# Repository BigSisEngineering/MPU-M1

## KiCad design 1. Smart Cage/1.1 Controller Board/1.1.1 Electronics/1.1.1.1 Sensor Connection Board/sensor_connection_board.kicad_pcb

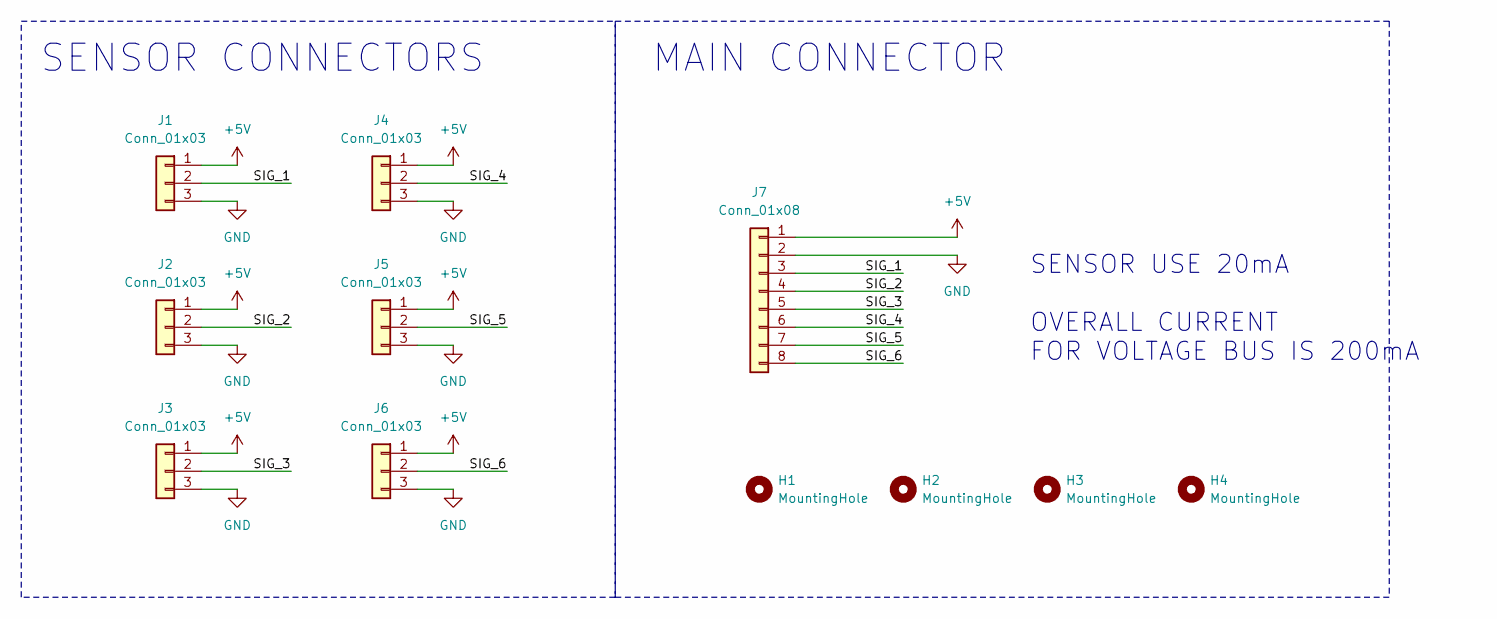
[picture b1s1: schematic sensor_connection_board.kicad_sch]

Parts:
H1, H2, H3, H4: MountingHole; MountingHole_3.2mm_M3_ISO7380
J1, J2, J3, J4, J5, J6: Conn_01x03; JST_PH_B3B-PH-K_1x03_P2.00mm_Vertical; LCSC C131339
J7: Conn_01x08; JST_PH_B8B-PH-K_1x08_P2.00mm_Vertical; LCSC C157974

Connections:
+5V: J1.1, J2.1, J3.1, J4.1, J5.1, J6.1, J7.1
/SIG_1: J1.2, J7.3
/SIG_2: J2.2, J7.4
/SIG_3: J3.2, J7.5
/SIG_4: J4.2, J7.6
/SIG_5: J5.2, J7.7
/SIG_6: J6.2, J7.8
GND: J1.3, J2.3, J3.3, J4.3, J5.3, J6.3, J7.2

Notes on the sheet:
MAIN CONNECTOR
SENSOR USE 20mA OVERALL CURRENT FOR VOLTAGE BUS IS 200mA
SENSOR CONNECTORS

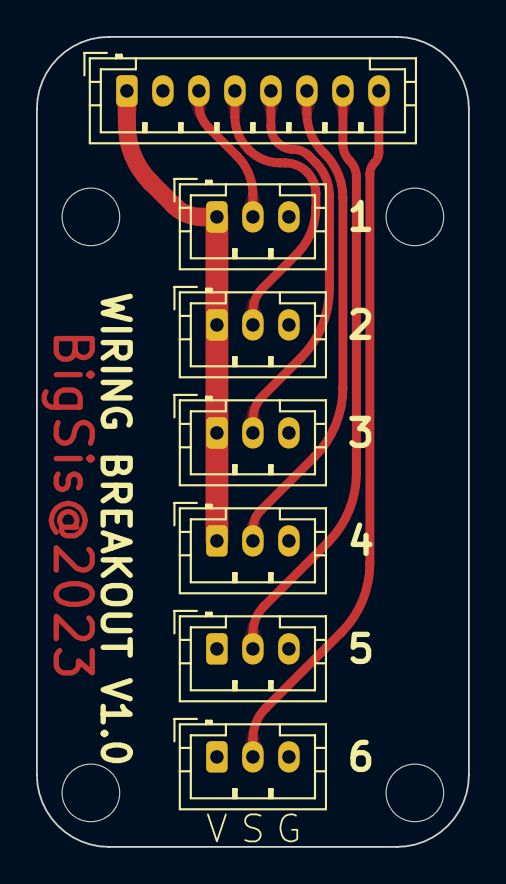
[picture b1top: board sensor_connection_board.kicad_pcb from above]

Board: 2 copper layers, 24.0 x 45.0 mm, 11 parts (0 on the bottom side), 8 nets.

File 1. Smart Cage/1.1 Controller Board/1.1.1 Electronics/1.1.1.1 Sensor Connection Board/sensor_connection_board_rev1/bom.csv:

Designator,Footprint,Quantity,Value,LCSC Part #
"H1, H2, H3, H4",MountingHole_3.2mm_M3_ISO7380,4,MountingHole,
"J1, J2, J3, J4, J5, J6",JST_PH_B3B-PH-K_1x03_P2.00mm_Vertical,6,Conn_01x03,C131339
J7,JST_PH_B8B-PH-K_1x08_P2.00mm_Vertical,1,Conn_01x08,C157974

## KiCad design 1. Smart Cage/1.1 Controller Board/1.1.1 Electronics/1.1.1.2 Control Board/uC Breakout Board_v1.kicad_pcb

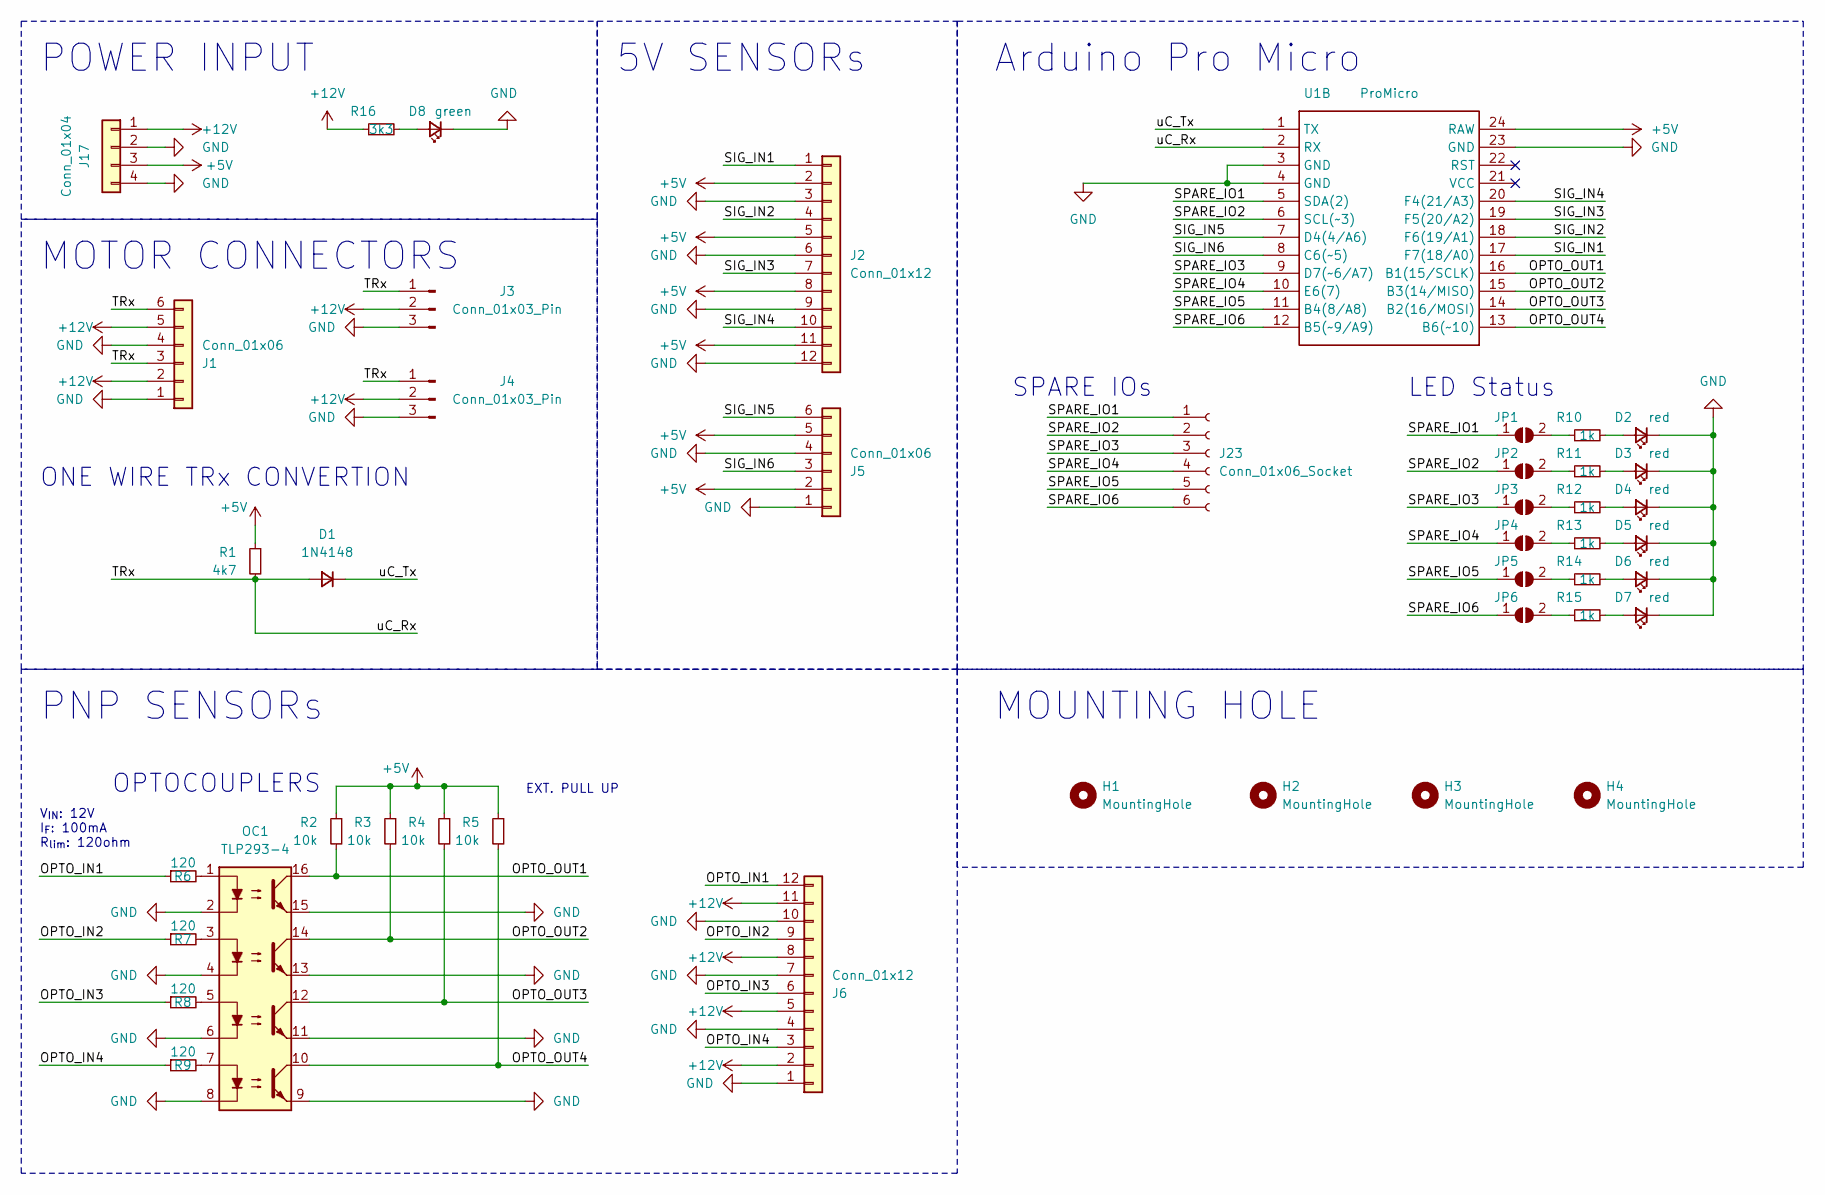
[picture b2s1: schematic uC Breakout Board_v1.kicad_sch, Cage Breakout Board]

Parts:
D1: 1N4148; D_SOD-123; LCSC C81598
D2, D3, D4, D5, D6, D7: red; LED_0805_2012Metric_Pad1.15x1.40mm_HandSolder; LCSC C434431
D8: green; LED_0805_2012Metric_Pad1.15x1.40mm_HandSolder; LCSC C434435
H1, H2, H3, H4: MountingHole; MountingHole_3.2mm_M3_ISO7380
J1, J5: Conn_01x06; DB142R-5.08-6P; LCSC C2898713
J2, J6: Conn_01x12; DB142R-5.08-12P; LCSC C2898718
J3, J4: Conn_01x03_Pin; PinSocket_1x03_P2.54mm_Vertical
J17: Conn_01x04; DB142R-5.08-4P; LCSC C2898711
J23: Conn_01x06_Socket; PinHeader_1x06_P2.54mm_Vertical
JP1, JP2, JP3, JP4, JP5, JP6: SolderJumper_2_Open; SolderJumper-2_P1.3mm_Open_TrianglePad1.0x1.5mm
OC1: TLP293-4; SOIC-16W_5.3x10.2mm_P1.27mm; LCSC C3002262
R1: 4k7; R_0805_2012Metric_Pad1.20x1.40mm_HandSolder; LCSC C229219
R2, R3, R4, R5: 10k; R_0805_2012Metric_Pad1.20x1.40mm_HandSolder; LCSC C84376
R6, R7, R8, R9: 120; R_0805_2012Metric_Pad1.20x1.40mm_HandSolder; LCSC C114244
R10, R11, R12, R13, R14, R15: 1k; R_0805_2012Metric_Pad1.20x1.40mm_HandSolder; LCSC C95781
R16: 3k3; R_0805_2012Metric_Pad1.20x1.40mm_HandSolder; LCSC C114531
U1: ProMicro; ProMicro-2x12-Header-B; LCSC C3975157
U2: ProMicro; ProMirco-2x12-Header-A; LCSC C3975157

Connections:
+5V: J2.2, J2.5, J2.8, J2.11, J5.2, J5.5, J17.3, R1.1, R2.1, R3.1, R4.1, R5.1, U1.24 (RAW)
+12V: J1.2, J1.5, J3.2, J4.2, J6.2, J6.5, J6.8, J6.11, J17.1, R16.1
/OPTO_IN1: J6.12, R6.1
/OPTO_IN2: J6.9, R7.1
/OPTO_IN3: J6.6, R8.1
/OPTO_IN4: J6.3, R9.1
/OPTO_OUT1: OC1.16, R2.2, U1.16 (B1(15/SCLK))
/OPTO_OUT2: OC1.14, R3.2, U1.15 (B3(14/MISO))
/OPTO_OUT3: OC1.12, R4.2, U1.14 (B2(16/MOSI))
/OPTO_OUT4: OC1.10, R5.2, U1.13 (B6(~10))
/SIG_IN1: J2.1, U1.17 (F7(18/A0))
/SIG_IN2: J2.4, U1.18 (F6(19/A1))
/SIG_IN3: J2.7, U1.19 (F5(20/A2))
/SIG_IN4: J2.10, U1.20 (F4(21/A3))
/SIG_IN5: J5.6, U2.7 (D4(4/A6))
/SIG_IN6: J5.3, U2.8 (C6(~5))
/SPARE_IO1: J23.1, JP1.1 (A), U2.5 (SDA(2))
/SPARE_IO2: J23.2, JP2.1 (A), U2.6 (SCL(~3))
/SPARE_IO3: J23.3, JP3.1 (A), U2.9 (D7(~6/A7))
/SPARE_IO4: J23.4, JP4.1 (A), U2.10 (E6(7))
/SPARE_IO5: J23.5, JP5.1 (A), U2.11 (B4(8/A8))
/SPARE_IO6: J23.6, JP6.1 (A), U2.12 (B5(~9/A9))
/TRx: D1.2 (A), J1.3, J1.6, J3.1, J4.1, R1.2, U2.2 (RX)
/uC_Tx: D1.1 (K), U2.1 (TX)
GND: D2.1 (K), D3.1 (K), D4.1 (K), D5.1 (K), D6.1 (K), D7.1 (K), D8.1 (K), J1.1, J1.4, J2.3, J2.6, J2.9, J2.12, J3.3, J4.3, J5.1, J5.4, J6.1, J6.4, J6.7, J6.10, J17.2, J17.4, OC1.2, OC1.4, OC1.6, OC1.8, OC1.9, OC1.11, OC1.13, OC1.15, U1.23 (GND), U2.3 (GND), U2.4 (GND)
unnamed: D2.2 (A), R10.2
unnamed: D3.2 (A), R11.2
unnamed: D4.2 (A), R12.2
unnamed: D5.2 (A), R13.2
unnamed: D6.2 (A), R14.2
unnamed: D7.2 (A), R15.2
unnamed: D8.2 (A), R16.2
unnamed: JP1.2 (B), R10.1
unnamed: JP2.2 (B), R11.1
unnamed: JP3.2 (B), R12.1
unnamed: JP4.2 (B), R13.1
unnamed: JP5.2 (B), R14.1
unnamed: JP6.2 (B), R15.1
unnamed: OC1.1, R6.2
unnamed: OC1.3, R7.2
unnamed: OC1.5, R8.2
unnamed: OC1.7, R9.2

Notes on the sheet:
OPTOCOUPLERS
Arduino Pro Micro
ONE WIRE TRx CONVERTION
LED Status
V_{IN}: 12V I_{F}: 100mA R_{lim}: 120ohm
MOTOR CONNECTORS
POWER INPUT
MOUNTING HOLE
5V SENSORs
PNP SENSORs
SPARE IOs
EXT. PULL UP

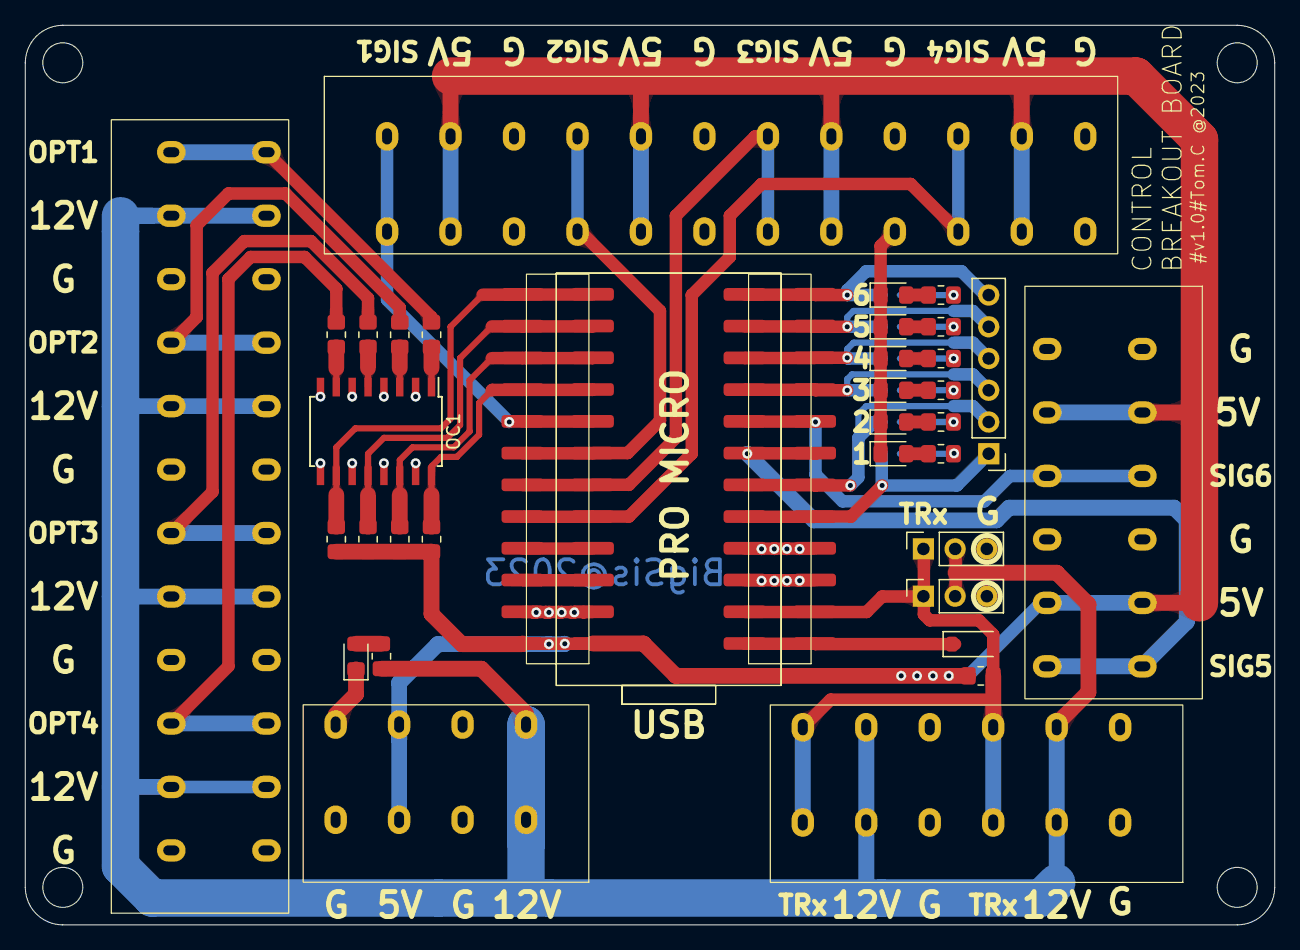
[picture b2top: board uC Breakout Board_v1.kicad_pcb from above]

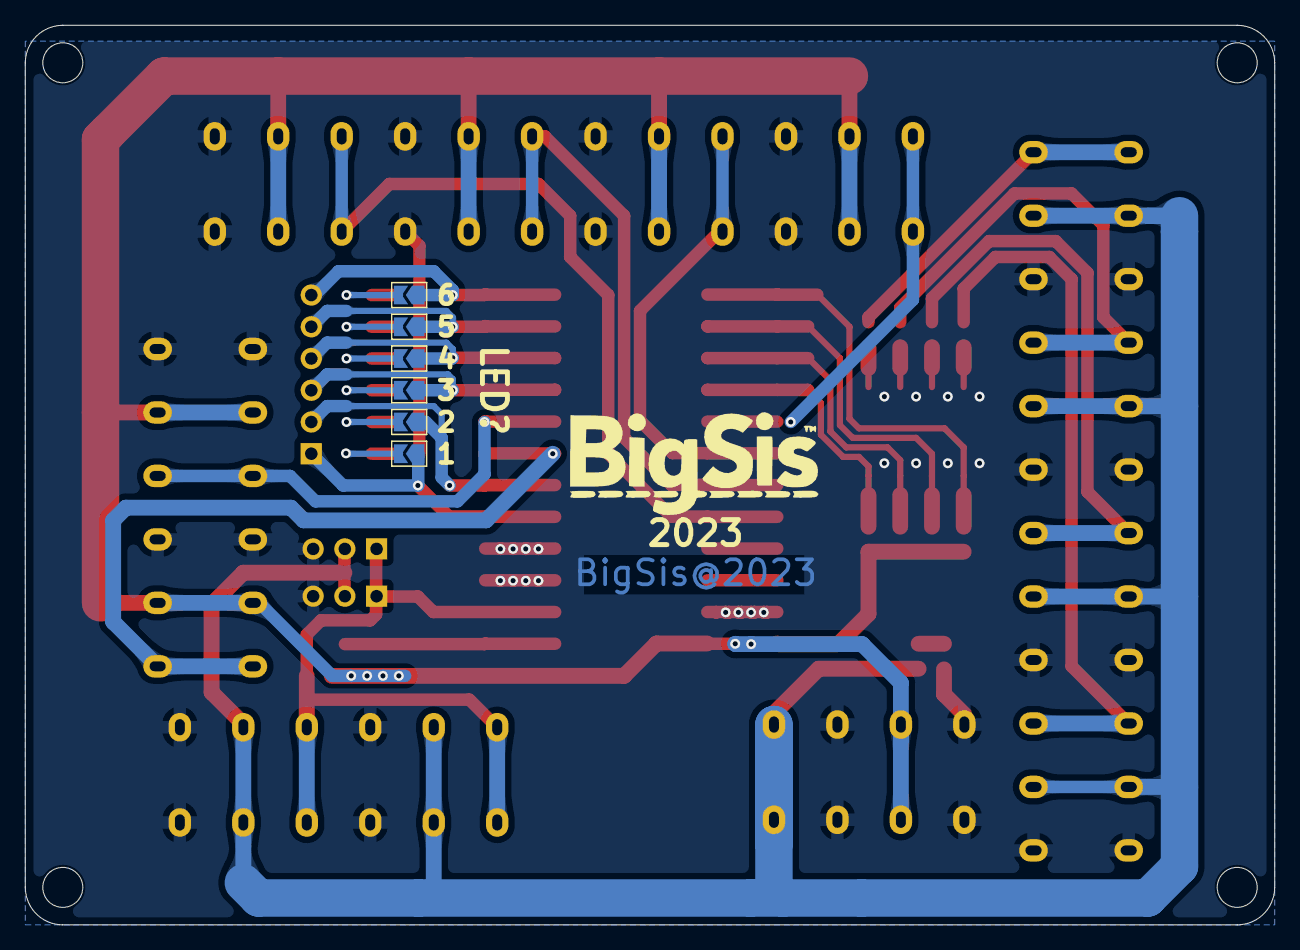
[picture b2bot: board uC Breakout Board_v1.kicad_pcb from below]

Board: 2 copper layers, 100.0 x 72.0 mm, 45 parts (6 on the bottom side), 42 nets.

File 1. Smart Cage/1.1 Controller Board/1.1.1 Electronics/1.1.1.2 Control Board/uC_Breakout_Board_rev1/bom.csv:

Designator,Footprint,Quantity,Value,LCSC Part #
D1,D_SOD-123,1,1N4148,C81598
"D2, D3, D4, D5, D6, D7",0805,6,red,C434431
D8,0805,1,green,C434435
"H1, H2, H3, H4",MountingHole_3.2mm_M3_ISO7380,4,MountingHole,
"J1, J5",DB142R-5.08-6P,2,Conn_01x06,C2898713
J17,DB142R-5.08-4P,1,Conn_01x04,C2898711
"J2, J6",DB142R-5.08-12P,2,Conn_01x12,C2898718
J23,PinHeader_1x06_P2.54mm_Vertical,1,Conn_01x06_Socket,
"J3, J4",PinSocket_1x03_P2.54mm_Vertical,2,Conn_01x03_Pin,
"JP1, JP2, JP3, JP4, JP5, JP6",SolderJumper-2_P1.3mm_Open_TrianglePad1.0x1.5mm,6,SolderJumper_2_Open,
OC1,SOIC-16W_5.3x10.2mm_P1.27mm,1,TLP293-4,C3002262
R1,0805,1,4k7,C229219
"R10, R11, R12, R13, R14, R15",0805,6,1k,C95781
R16,0805,1,3k3,C114531
"R2, R3, R4, R5",0805,4,10k,C84376
"R6, R7, R8, R9",0805,4,120,C114244
U1,ProMicro-2x12-Header-B,1,ProMicro,C3975157
U2,ProMirco-2x12-Header-A,1,ProMicro,C3975157

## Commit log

2024-03-19 Add files via upload
    first commit
2024-04-05 [BACKEND] Integrated 1c backend. [UI] Added 'Start 1C' and 'Stop 1C' buttons
2024-04-12 fixed trapping webpage
2024-04-12 connected buttons to the server
2024-04-15 circular mask
2024-04-16 completing js webapp
2024-04-17 connected buttons to endpoints
2024-04-18 master control beta
2024-04-21 front end
2024-05-28 - Removed streamlit dependency - Implemented cycle_time for pnp. Defaults to 6seconds.
2024-05-28 fixed handler
2024-05-28 REMOVED ALL STREAMLIT
2024-05-28 disabled heartbeat. Moved http server to main thread
2024-05-28 fixed delay
2024-05-28 20 sec logic for the sensors
2024-05-28 Revert "merge main into m1c-integration"
2024-05-30 setup bash update
2024-05-30 setup.sh complete
2024-05-30 real time sync fix
2024-05-31 upstream control
2024-05-31 Added Arduino Code
2024-05-31 removed heartbeat thread
2024-05-31 blabla
2024-05-31 moved exec_action from main to http_cage
2024-05-31 setup.sh
2024-05-31 get pot now happens in threads
2024-06-03 front end update
2024-06-03 added lock to find circle. Recorded additional dependencies
2024-06-04 buttons a2 and a3
2024-06-05 diet dispenser buttons
2024-06-05 auto untick chebox for action selection
2024-06-05 added endpoint to init unloader and sw
2024-06-07 fixed pnp dummy toggle
2024-06-10 SW indicator turns grey after clearing error
2024-06-10 push
2024-06-11 diet dispenser actions are now controlled by flags
2024-06-11 background task handler
2024-06-12 added logic to block exec button more than 3 times in a min
2024-06-12 removed threshold for pot request
2024-06-13 trying to get
2024-06-13 accumulated pots fix
2024-06-17 ignore
2024-06-17 added watchdog to FindCircleThread
2024-06-17 display camera error
2024-06-17 5.0.2-b
2024-06-17 update fix
2024-06-19 Now prevent PNP or DUMMY to start if servos not init
2024-06-19 a3 will now stop first before a1 is stopped
2024-06-20 first flask app running on r2
2024-06-20 pop ou message for nozzle
2024-06-20 init at start and auto clear error logic
2024-06-20 Init servos at the boot and attempt to re-init if servos errors
2024-06-21 auto init bug fix
2024-06-24 implemented data upload for A2
2024-06-24 fixed variable to change sw speed
2024-06-25 a2 data complete
2024-06-25 added log file for MasterApp
2024-06-25 [WEBAPP] hardcoded ROW -> dynamic ROW
2024-06-25 bug fix
2024-06-25 Increased camera resolution
2024-06-25 added function to send_script to restart webapp
2024-06-26 setup for rock 5a
2024-06-27 fixed sw homing issue on new sw. if homing sensor is high sw will move untill it becomes low & viceversa
2024-06-28 added image logger
2024-07-09 removed on9 stuff
2024-07-12 bbox on preview
2024-07-12 sw not home indicator added
2024-07-19 timer to 6h
2024-07-20 DietHeater_Code
2024-07-25 added overload logic to the unloader
2024-07-26 added watchdog to reset the arduino
2024-07-30 uidev
2024-07-31 ui comm
2024-08-02 react dev
2024-08-02 flask
2024-08-05 setup.sh. Refresh only onerror
2024-08-05 catch for whole cage dict
2024-08-05 remove debug code
2024-08-05 temp
2024-08-05 hostname now matches with .local suffix
2024-08-13 module and row no longer depends on hostname
2024-08-21 added experiment mode
2024-09-02 react app
2024-09-12 added experiment mode set pause interval
2024-10-03 socketio
2024-10-03 CLI for tasks
2024-10-03 removed emit lock. Cage dict transmitted every 5 seconds
2024-10-03 removed 5s cage dict send. No visible improvement
2024-10-03 Session now sends before Info
2024-10-07 formatter
2024-10-08 max timeout counter to prevent old value from being held forever
2024-10-08 updated requirements.txt
2024-10-10 - socket transmission delay from 0.1 seconds to 1 seconds. - LastPing initialized as time website accessed instead of null
2024-10-22 maintainence flag
2024-10-22 reduce opacity for maintainence cages
2024-10-22 unblocking initialization
2024-10-22 mega unblocking
2024-10-24 removed redundant locks
2024-10-24 glen experiment mode
2024-10-24 start experiment handles time stamp
2024-10-24 added glen experiment stuff
2024-10-24 added read experiment status
2024-10-24 exec action on cage now holds the lock
2024-10-24 added staggered start
2024-10-24 board timer shenanigans
2024-10-24 confusion
2024-10-24 more confusion
2024-10-25 move start delay adjustments
2024-10-25 pythonic naming update
2024-10-25 experiment sequence change
2024-10-25 dummy pnp and experiment starts regardless of servo and camera state
2024-10-25 fixed ask_sensors returning non-type on error
2024-10-25 removed fixme
2024-10-25 another mega unblock
2024-10-25 experiment status will keep updating regardless of execute flag
2024-10-25 data fetch for experiment now happens at the beginning of the loop
2024-10-25 using server time instead of local timestamp
2024-10-25 removed temp experiment code
2024-10-25 working
2024-10-25 tidied up code. Tan signing off
2024-10-25 easy clap
2024-10-28 fetch pot now uses lock unconditionally
2024-10-28 use purge timer (NOT YET EXPOSED)
2024-10-28 major pot request fix
2024-10-28 fixed tmp_egg_pot_counter
2024-10-28 experiment mode status
2024-10-28 update for master UI display
2024-10-28 experiment mode dev complete
2024-10-29 experiment mode display complete
2024-10-29 updated gitignore
2024-10-29 gitignore
2024-10-30 further optimization
2024-10-30 log pattern change
2024-10-30 index_ui convert from float to int
2024-10-30 updated key
2024-10-30 Fixed index shift master UI display
2024-10-30 print bug fix + logging update
2024-10-30 Non blocking initialization
2024-10-30 debouncing for status code
2024-10-30 removed redundant code
2024-10-30 commented some code
2024-10-30 status code now updates at initialize wait as well
2024-10-30 differentiate init wait and normal wait
2024-10-30 frontend update to display the 2 new status codes
2024-10-30 UI sensor mode and action mode
2024-10-30 status code update
2024-10-30 bug fix for m1a buttons
2024-10-30 unset UI debug flag
2024-10-30 enable and disable experiment now restarts counter
2024-10-31 swap sequence number and sequence index position at cage UI
2024-10-31 additional logging
2024-10-31 cage react fix
2024-10-31 cage UI bug fix
2024-10-31 fixed bug where sw error is being assigned as ul error
2024-11-01 cage score backend complete
2024-11-01 daily reset for cage score
2024-11-07 master ui support
2024-11-07 opacity now changes according to purge frequence. Fallback state available for old cage software
2024-11-14 unload sensor, valve control
2024-11-18 minutes to second (glen)
2024-11-19 Added purge frequency for 3 mins pause interval. Reworked blasting logic
2024-11-21 valve blast tmp
2024-11-21 dissociated all blast from sw movements
2024-11-26 Fixed is_servo_ready not returning boolean
2024-11-28 added 0 mins setting
2024-11-29 code cleanup
2024-12-10 status 17 into master display
2024-12-10 1A 1C backend optimization
2024-12-10 separated fetch pot loop
2024-12-10 cage score minor fix
2024-12-10 naming
2024-12-10 set zero resets num_pots too
2024-12-10 added status code for 1A
2024-12-10 UI support for 1a status code
2024-12-11 Modified UI. Added CLEAR UL ERROR button to cage control
2024-12-11 increased max sessions
2024-12-11 documentation added
2024-12-11 arduino doc
2024-12-11 page navigation for master
2024-12-11 build
2024-12-11 react-master code cleanup
2024-12-12 added favicon in assets
2024-12-12 img link change now instantly prompts refresh
2024-12-12 readded AlertBox
2024-12-13 value of get_info/m1a and m1c is no longer in string format. Comissioned master debugging page
